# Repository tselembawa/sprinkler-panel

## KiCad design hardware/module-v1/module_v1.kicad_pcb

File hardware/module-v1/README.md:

# Module 4/4, PCB v1 (όλα THT, 100 × 100 mm)

Πλακέτα-βάση για το NUCLEO-G031K8: τροφοδοσία 24 V, RS485 (MAX3485), 4 είσοδοι EOL, 4 ρελέ
changeover, DIP διεύθυνσης με LED. Σχέδιο και αποφάσεις: [docs/module-pcb-v1.md](../../docs/module-pcb-v1.md).

| Αρχείο | Τι είναι |
| --- | --- |
| `module_v1.kicad_pro` | το project: αυτό ανοίγεις στο KiCad |
| `module_v1.kicad_sch` | σχηματικό (οι συνδέσεις γίνονται με ετικέτες ίδιου ονόματος) |
| `module_v1.kicad_pcb` | πλακέτα με τα εξαρτήματα **τοποθετημένα**, χωρίς διαδρόμους ακόμα |
| `bom.csv` | λίστα υλικών |
| `placement.png` | πώς είναι τοποθετημένα (προεπισκόπηση) |
| `parts.py`, `gen.py` | από εδώ βγαίνουν τα παραπάνω (`python gen.py <kicad-footprints>`) |

## Βήματα στο KiCad (8 ή 9)

1. Άνοιξε το `module_v1.kicad_pro`. Αν πει ότι η πλακέτα είναι σε παλιά μορφή και θα μετατραπεί: **OK**.
2. **Σχηματικό**: Inspect → **Electrical Rules Checker** → Run. Στείλε μου ό,τι βγάλει.
3. **PCB Editor**: Tools → **Update PCB from Schematic** (F8). Αν θέλει να **προσθέσει** εξαρτήματα
   (αντί να βρει τα υπάρχοντα), τσέκαρε το **«Re-link footprints to schematic symbols based on their
   reference designators»** και μετά Update. Δεν πρέπει να αλλάξει σχεδόν τίποτα· αν βγάλει λάθη,
   στείλε μου screenshot.
4. **Δρομολόγηση με Freerouting**: Plugin and Content Manager → «Freerouting» → Install.
   Μετά στο PCB: Tools → External Plugins → Freerouting → Start. Περιμένει μερικά λεπτά.
5. Πάτα **B** (γεμίζει η γείωση στην κάτω πλευρά).
6. Inspect → **Design Rules Checker** → Run DRC. Στείλε μου screenshot με τα σφάλματα.
7. Μόνο όταν είναι καθαρό: File → Fabrication Outputs → Gerbers + Drill → zip → JLCPCB.

Οι διάδρομοι για 24 V, GND, 5 V και τις επαφές των ρελέ είναι 1 mm (net class «Power»), το 24 V
του bus από X1 σε X2 2 mm (net class «Bus»), τα σήματα 0,3 mm.

## Πριν την παραγγελία: έλεγχοι με το Nucleo στο χέρι

1. ~~Ποια πλευρά είναι το CN3~~: επιβεβαιωμένο. Με το USB **προς τα πάνω**: CN3 (D1, D0, RST, GND, D2…)
   **αριστερά**, CN4 (VIN, GND, RST, +5V, A7…) **δεξιά**, **pin 1 πάνω** δίπλα στο USB.
2. **Το jumper D2–GND** του Nucleo (CN3 pin 4–5) βγαίνει.
3. **Ρελέ SRD**: το KiCad λέει pin 3 = NO, pin 4 = NC. Με το πρώτο ρελέ στο χέρι, με πολύμετρο:
   ανάμεσα στο COM και στο NC πρέπει να **χτυπάει** (κλειστή) χωρίς τάση στο πηνίο.
4. **Πόσο προεξέχει το Nucleo**: μέτρησε από το κέντρο του pin 1 (D1) μέχρι την άκρη της πλακέτας
   του Nucleo προς το USB, και από το pin 15 (D12) μέχρι την άλλη άκρη. Στο PCB υπάρχουν 12 mm προς
   το USB και 9 mm προς την άλλη πλευρά (μετά είναι η βάση του ULN2003).
5. **A4 και A5 στο breadboard** (δεν έχουν δοκιμαστεί ακόμα): DIP8 μόνο του ON + restart → διεύθυνση 128·
   και το `MOD_DE_PIN` με RS485 module που έχει DE/RE, αν υπάρχει.

## Τι αγοράζεις επιπλέον (δεν είναι στο bom.csv)

- 2 × θηλυκή κεφαλή 1×15, 2,54 mm (για το Nucleo)
- βάση DIP-8 και βάση DIP-16 (για MAX3485 και ULN2003A)
- 1 jumper 2,54 mm (τερματισμός 120 Ω)
- 4 × βίδα M3 + αποστάτες

## Firmware

Στο `firmware/module/mod_app.c`: `#define MOD_BOARD_PCB_V1 1` (DE στο A5, μέτρηση 24 V στο A6).
Στο breadboard μένει `0`.

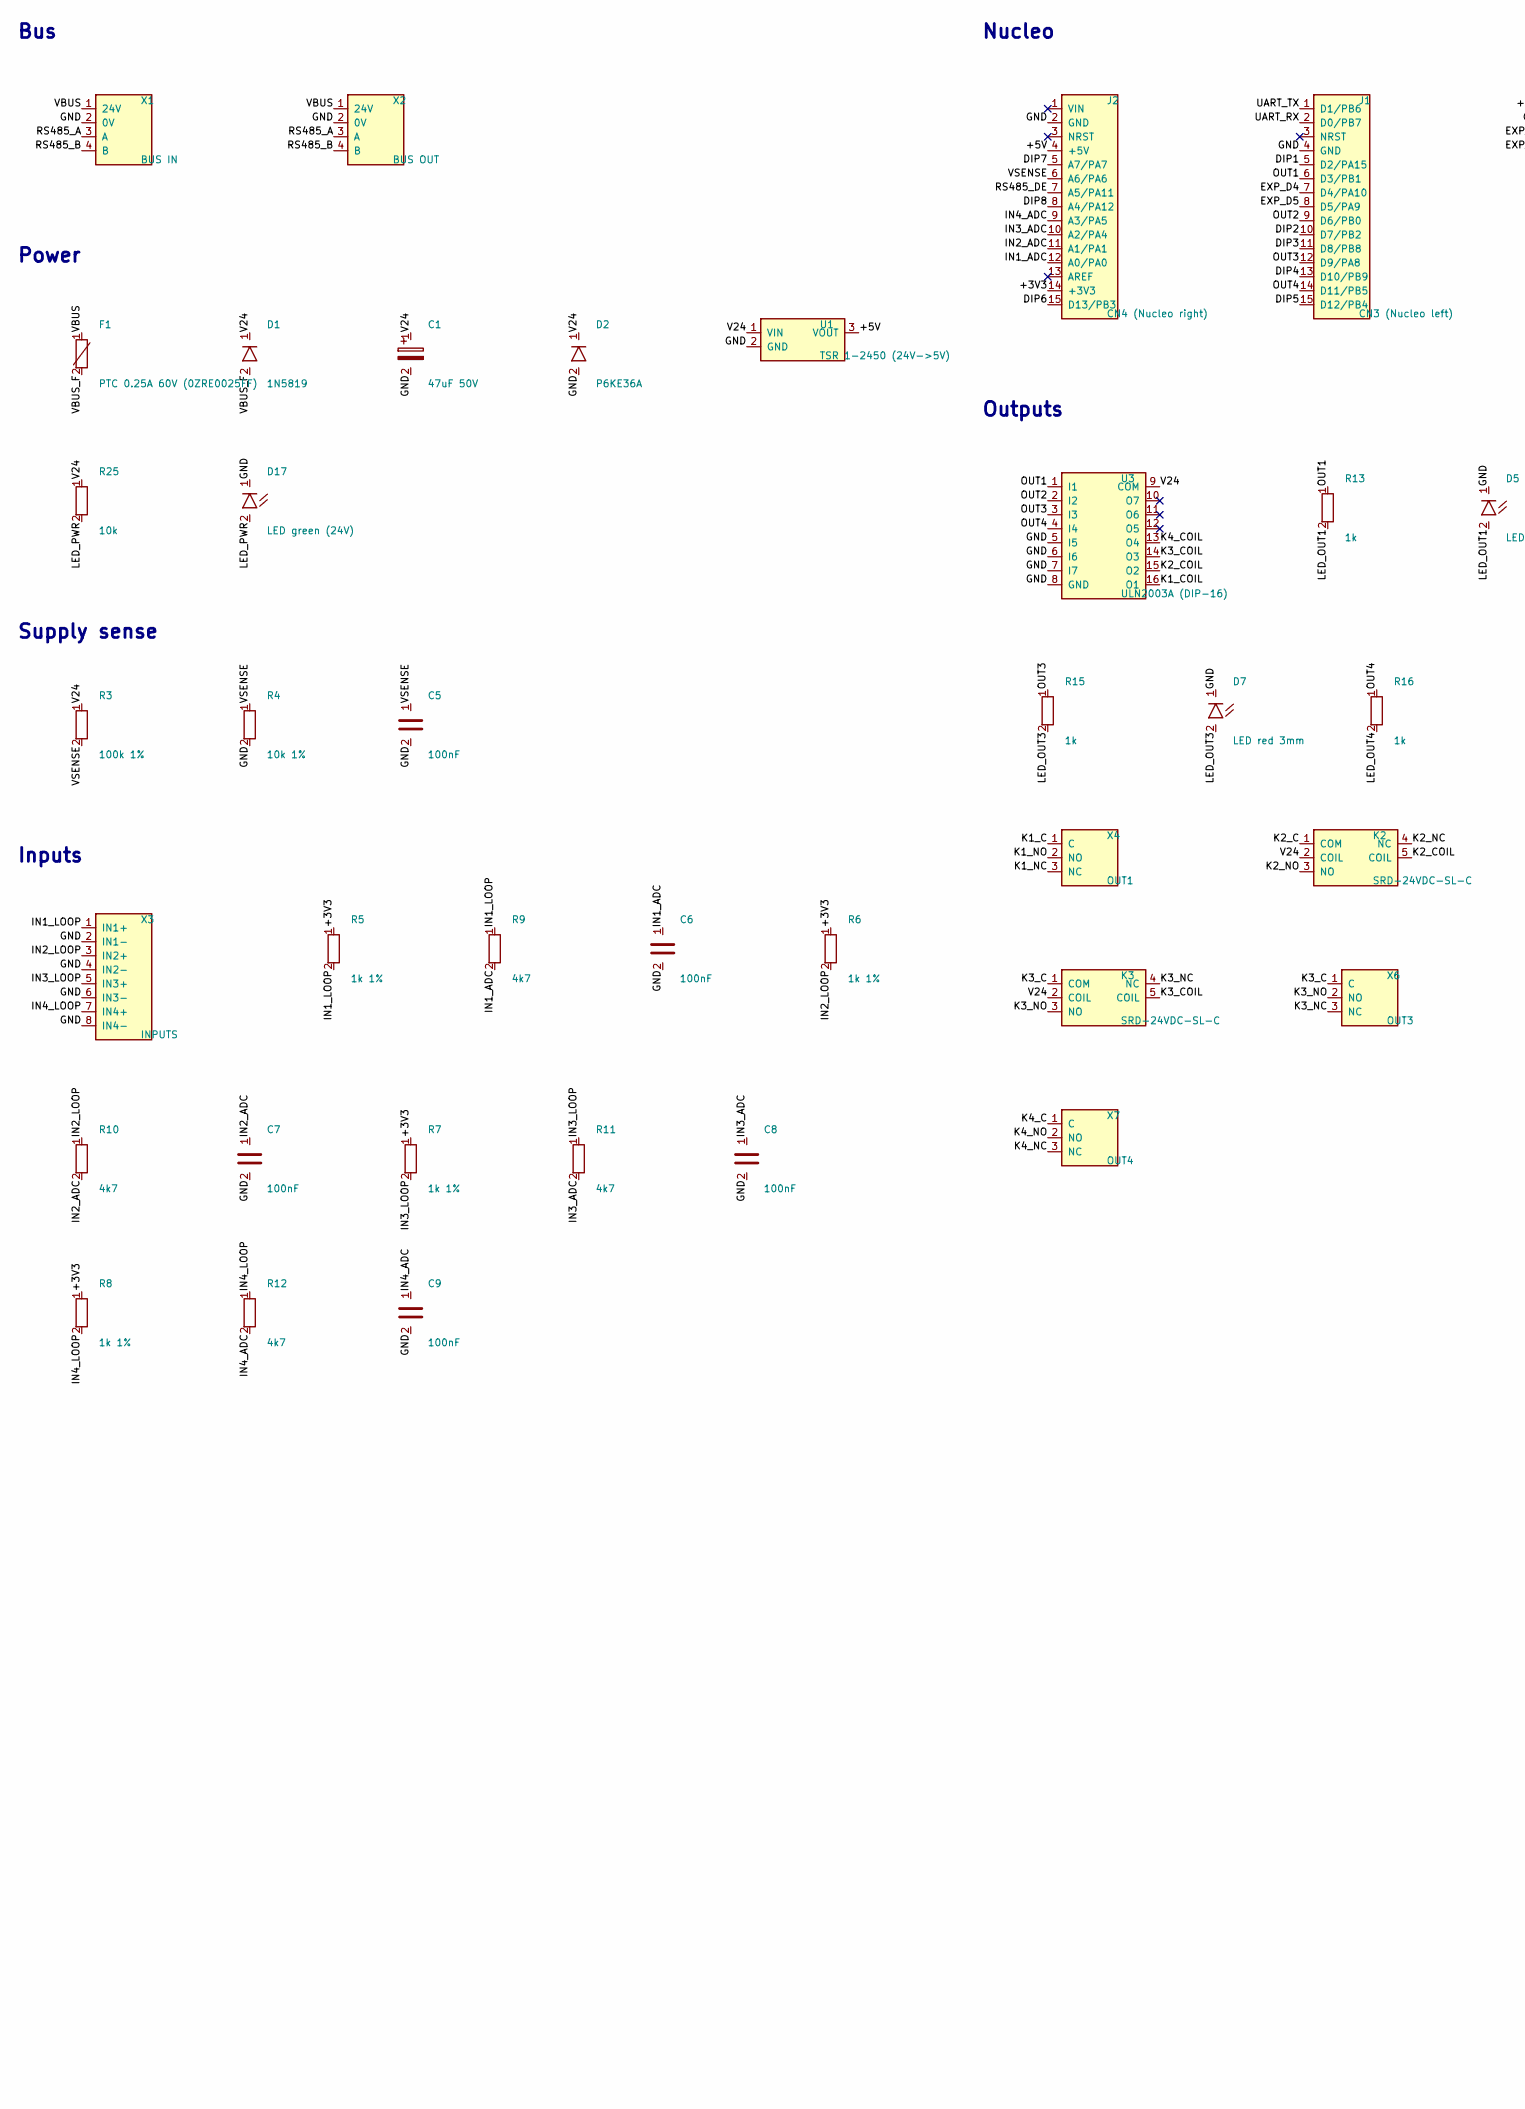
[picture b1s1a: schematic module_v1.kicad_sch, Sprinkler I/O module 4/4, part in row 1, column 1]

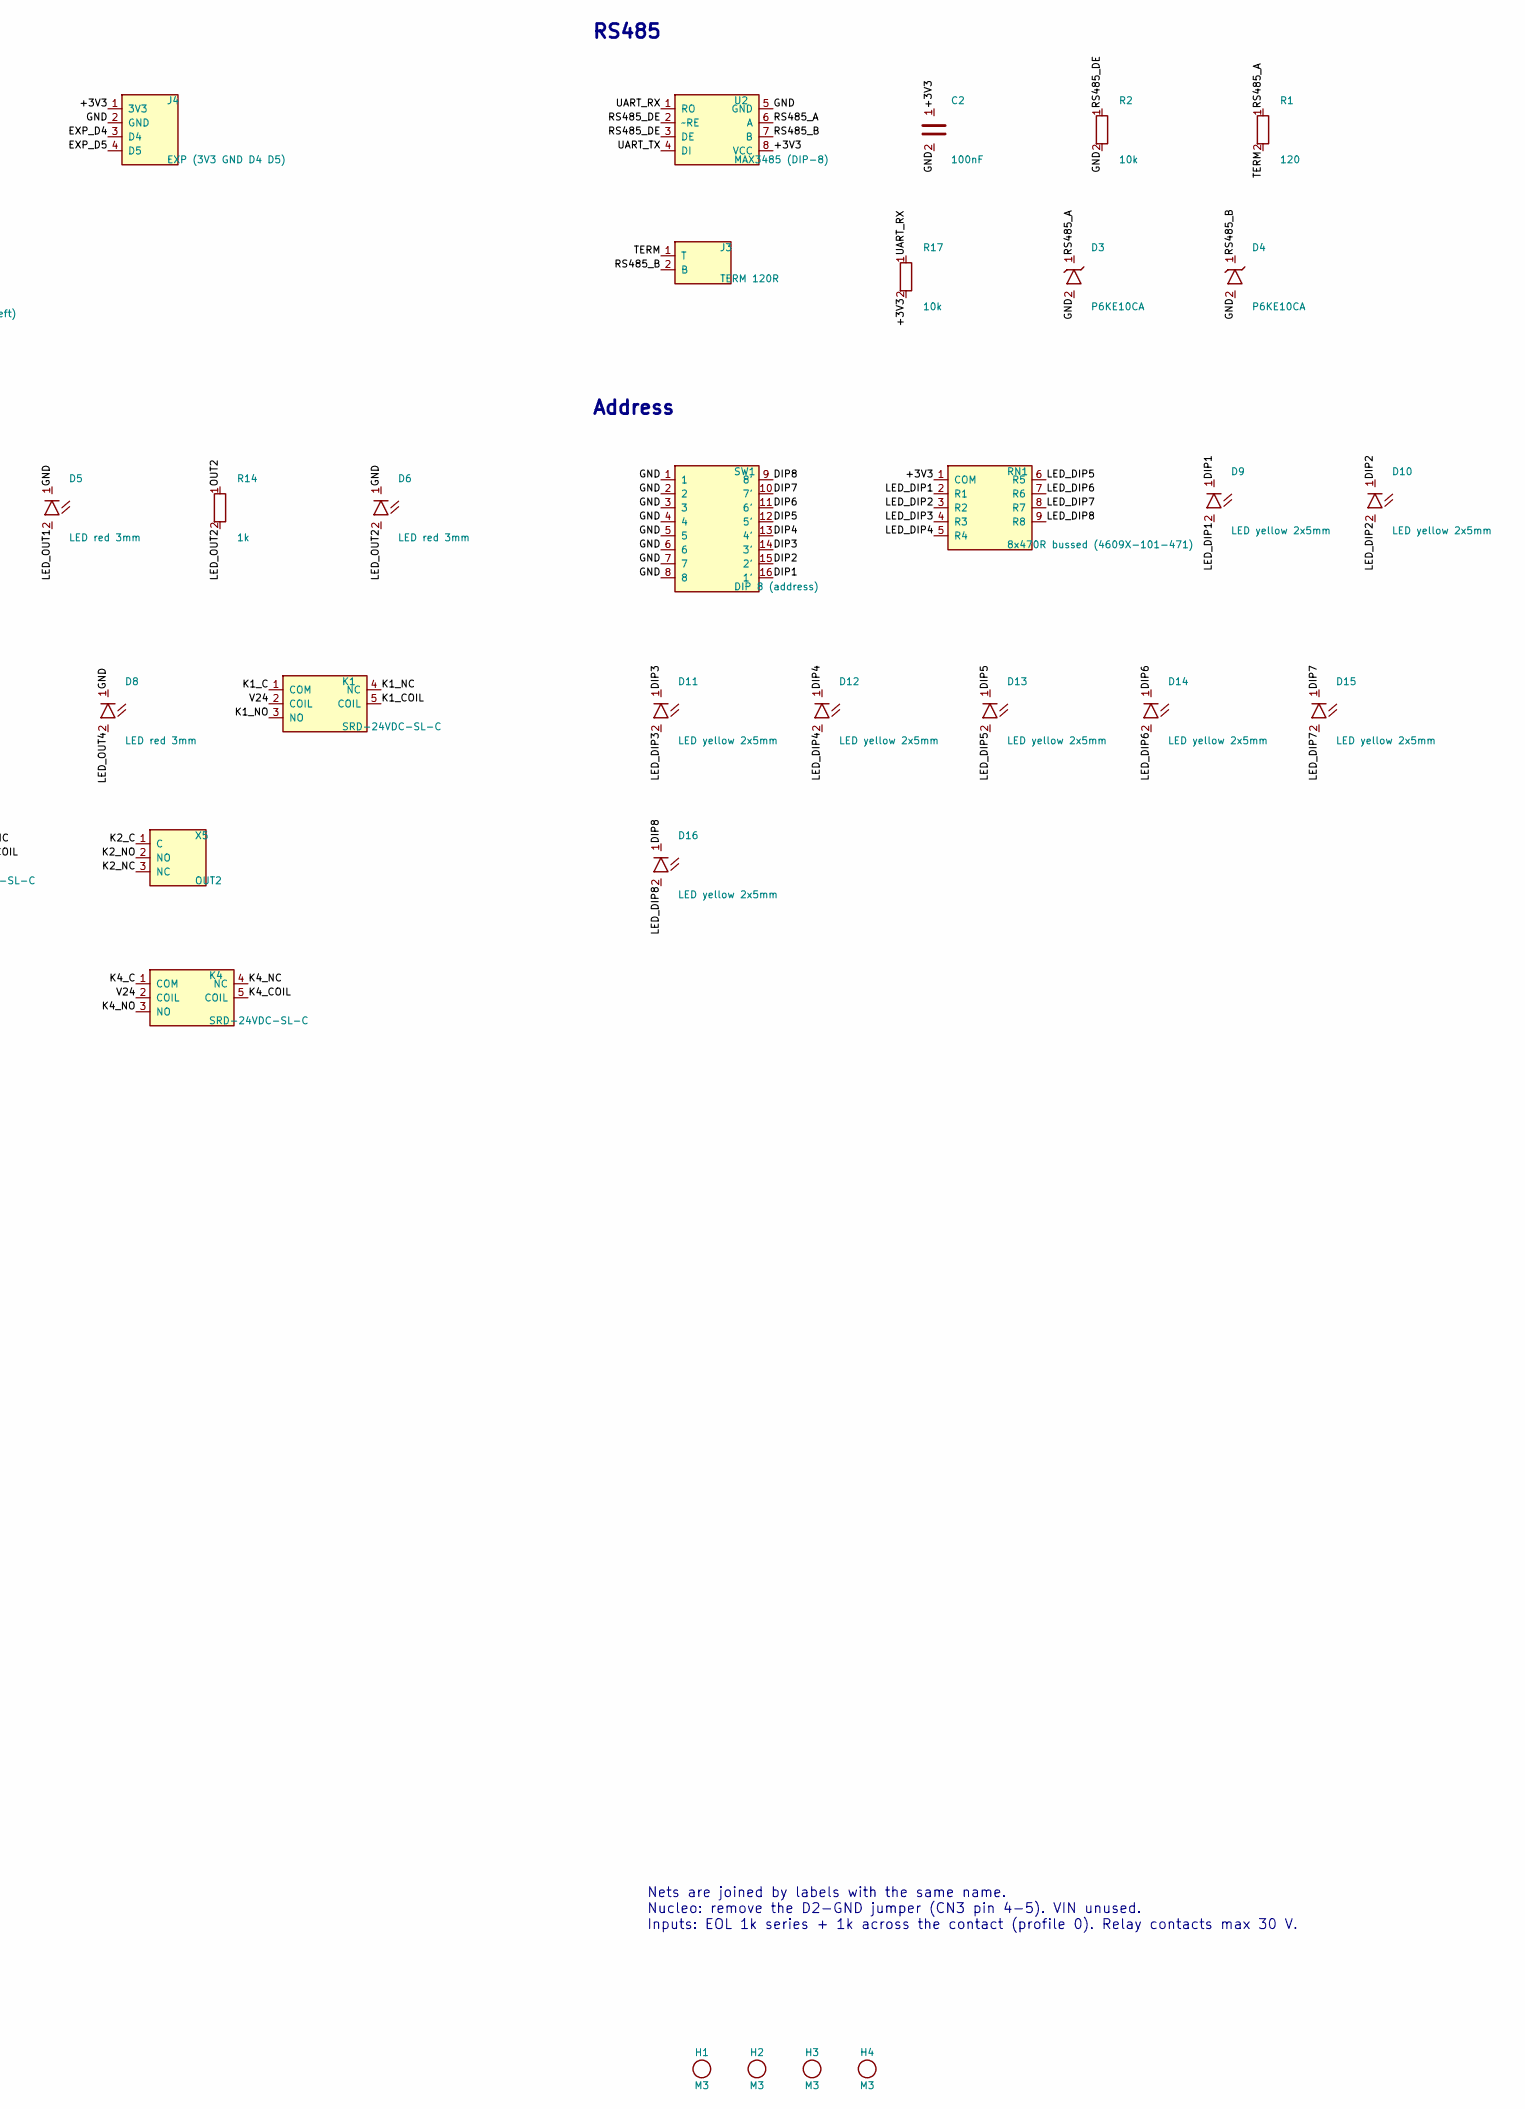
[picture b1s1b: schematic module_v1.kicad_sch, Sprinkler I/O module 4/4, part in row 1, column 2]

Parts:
C1: 47uF 50V; CP_Radial_D8.0mm_P3.50mm
C2, C5, C6, C7, C8, C9: 100nF; C_Disc_D5.0mm_W2.5mm_P5.00mm
D1: 1N5819; D_DO-41_SOD81_P10.16mm_Horizontal
D2: P6KE36A; D_DO-15_P12.70mm_Horizontal
D3, D4: P6KE10CA; D_DO-15_P5.08mm_Vertical_CathodeUp
D5, D6, D7, D8: LED red 3mm; LED_D3.0mm
D9, D10, D11, D12, D13, D14, D15, D16: LED yellow 2x5mm; LED_Rectangular_W5.0mm_H2.0mm
D17: LED green (24V); LED_D3.0mm
F1: PTC 0.25A 60V (0ZRE0025FF); Fuse_BelFuse_0ZRE0025FF_L9.6mm_W3.8mm
H1, H2, H3, H4: M3; MountingHole_3.2mm_M3
J1: CN3 (Nucleo left); PinSocket_1x15_P2.54mm_Vertical
J2: CN4 (Nucleo right); PinSocket_1x15_P2.54mm_Vertical
J3: TERM 120R; PinHeader_1x02_P2.54mm_Vertical
J4: EXP (3V3 GND D4 D5); PinHeader_1x04_P2.54mm_Vertical
K1, K2, K3, K4: SRD-24VDC-SL-C; Relay_SPDT_SANYOU_SRD_Series_Form_C
R1: 120; R_Axial_DIN0207_L6.3mm_D2.5mm_P7.62mm_Horizontal
R2: 10k; R_Axial_DIN0207_L6.3mm_D2.5mm_P7.62mm_Horizontal
R3: 100k 1%; R_Axial_DIN0207_L6.3mm_D2.5mm_P7.62mm_Horizontal
R4: 10k 1%; R_Axial_DIN0207_L6.3mm_D2.5mm_P7.62mm_Horizontal
R5, R6, R7, R8: 1k 1%; R_Axial_DIN0207_L6.3mm_D2.5mm_P7.62mm_Horizontal
R9, R10, R11, R12: 4k7; R_Axial_DIN0207_L6.3mm_D2.5mm_P7.62mm_Horizontal
R13, R14, R15, R16: 1k; R_Axial_DIN0207_L6.3mm_D2.5mm_P2.54mm_Vertical
R17, R25: 10k; R_Axial_DIN0207_L6.3mm_D2.5mm_P2.54mm_Vertical
RN1: 8x470R bussed (4609X-101-471); R_Array_SIP9
SW1: DIP 8 (address); SW_DIP_SPSTx08_Slide_9.78x22.5mm_W7.62mm_P2.54mm
U1: TSR 1-2450 (24V->5V); Converter_DCDC_RECOM_R-78E-0.5_THT
U2: MAX3485 (DIP-8); DIP-8_W7.62mm_Socket
U3: ULN2003A (DIP-16); DIP-16_W7.62mm_Socket
X1: BUS IN; TerminalBlock_Phoenix_MKDS-1,5-4-5.08_1x04_P5.08mm_Horizont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
X2: BUS OUT; TerminalBlock_Phoenix_MKDS-1,5-4-5.08_1x04_P5.08mm_Horizont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
X3: INPUTS; TerminalBlock_Phoenix_MKDS-1,5-8-5.08_1x08_P5.08mm_Horizont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
X4: OUT1; TerminalBlock_Phoenix_MKDS-1,5-3-5.08_1x03_P5.08mm_Horizont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
X5: OUT2; TerminalBlock_Phoenix_MKDS-1,5-3-5.08_1x03_P5.08mm_Horizont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
X6: OUT3; TerminalBlock_Phoenix_MKDS-1,5-3-5.08_1x03_P5.08mm_Horizont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
X7: OUT4; TerminalBlock_Phoenix_MKDS-1,5-3-5.08_1x03_P5.08mm_Horizont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

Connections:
+3V3: C2.1, J2.14 (+3V3), J4.1 (3V3), R5.1, R6.1, R7.1, R8.1, R17.2, RN1.1 (COM), U2.8 (VCC)
+5V: J2.4 (+5V), U1.3 (VOUT)
DIP1: D9.1, J1.5 (D2/PA15), SW1.16 (1')
DIP2: D10.1, J1.10 (D7/PB2), SW1.15 (2')
DIP3: D11.1, J1.11 (D8/PB8), SW1.14 (3')
DIP4: D12.1, J1.13 (D10/PB9), SW1.13 (4')
DIP5: D13.1, J1.15 (D12/PB4), SW1.12 (5')
DIP6: D14.1, J2.15 (D13/PB3), SW1.11 (6')
DIP7: D15.1, J2.5 (A7/PA7), SW1.10 (7')
DIP8: D16.1, J2.8 (A4/PA12), SW1.9 (8')
EXP_D4: J1.7 (D4/PA10), J4.3 (D4)
EXP_D5: J1.8 (D5/PA9), J4.4 (D5)
GND: C1.2, C2.2, C5.2, C6.2, C7.2, C8.2, C9.2, D2.2, D3.2, D4.2, D5.1, D6.1, D7.1, D8.1, D17.1, J1.4 (GND), J2.2 (GND), J4.2 (GND), R2.2, R4.2, SW1.1, SW1.2, SW1.3, SW1.4, SW1.5, SW1.6, SW1.7, SW1.8, U1.2 (GND), U2.5 (GND), U3.5 (I5), U3.6 (I6), U3.7 (I7), U3.8 (GND), X1.2 (0V), X2.2 (0V), X3.2 (IN1-), X3.4 (IN2-), X3.6 (IN3-), X3.8 (IN4-)
IN1_ADC: C6.1, J2.12 (A0/PA0), R9.2
IN1_LOOP: R5.2, R9.1, X3.1 (IN1+)
IN2_ADC: C7.1, J2.11 (A1/PA1), R10.2
IN2_LOOP: R6.2, R10.1, X3.3 (IN2+)
IN3_ADC: C8.1, J2.10 (A2/PA4), R11.2
IN3_LOOP: R7.2, R11.1, X3.5 (IN3+)
IN4_ADC: C9.1, J2.9 (A3/PA5), R12.2
IN4_LOOP: R8.2, R12.1, X3.7 (IN4+)
K1_C: K1.1 (COM), X4.1 (C)
K1_COIL: K1.5 (COIL), U3.16 (O1)
K1_NC: K1.4 (NC), X4.3 (NC)
K1_NO: K1.3 (NO), X4.2 (NO)
K2_C: K2.1 (COM), X5.1 (C)
K2_COIL: K2.5 (COIL), U3.15 (O2)
K2_NC: K2.4 (NC), X5.3 (NC)
K2_NO: K2.3 (NO), X5.2 (NO)
K3_C: K3.1 (COM), X6.1 (C)
K3_COIL: K3.5 (COIL), U3.14 (O3)
K3_NC: K3.4 (NC), X6.3 (NC)
K3_NO: K3.3 (NO), X6.2 (NO)
K4_C: K4.1 (COM), X7.1 (C)
K4_COIL: K4.5 (COIL), U3.13 (O4)
K4_NC: K4.4 (NC), X7.3 (NC)
K4_NO: K4.3 (NO), X7.2 (NO)
LED_DIP1: D9.2, RN1.2 (R1)
LED_DIP2: D10.2, RN1.3 (R2)
LED_DIP3: D11.2, RN1.4 (R3)
LED_DIP4: D12.2, RN1.5 (R4)
LED_DIP5: D13.2, RN1.6 (R5)
LED_DIP6: D14.2, RN1.7 (R6)
LED_DIP7: D15.2, RN1.8 (R7)
LED_DIP8: D16.2, RN1.9 (R8)
LED_OUT1: D5.2, R13.2
LED_OUT2: D6.2, R14.2
LED_OUT3: D7.2, R15.2
LED_OUT4: D8.2, R16.2
LED_PWR: D17.2, R25.2
OUT1: J1.6 (D3/PB1), R13.1, U3.1 (I1)
OUT2: J1.9 (D6/PB0), R14.1, U3.2 (I2)
OUT3: J1.12 (D9/PA8), R15.1, U3.3 (I3)
OUT4: J1.14 (D11/PB5), R16.1, U3.4 (I4)
RS485_A: D3.1, R1.1, U2.6 (A), X1.3 (A), X2.3 (A)
RS485_B: D4.1, J3.2 (B), U2.7 (B), X1.4 (B), X2.4 (B)
RS485_DE: J2.7 (A5/PA11), R2.1, U2.2 (~RE), U2.3 (DE)
TERM: J3.1 (T), R1.2
UART_RX: J1.2 (D0/PB7), R17.1, U2.1 (RO)
UART_TX: J1.1 (D1/PB6), U2.4 (DI)
V24: C1.1, D1.1, D2.1, K1.2 (COIL), K2.2 (COIL), K3.2 (COIL), K4.2 (COIL), R3.1, R25.1, U1.1 (VIN), U3.9 (COM)
VBUS: F1.1, X1.1 (24V), X2.1 (24V)
VBUS_F: D1.2, F1.2
VSENSE: C5.1, J2.6 (A6/PA6), R3.2, R4.1

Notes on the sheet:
Bus
Power
Supply sense
Inputs
Nucleo
Outputs
RS485
Address
Nets are joined by labels with the same name. Nucleo: remove the D2-GND jumper (CN3 pin 4-5). VIN unused. Inputs: EOL 1k series + 1k across the contact (profile 0). Relay contacts max 30 V.

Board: 2 copper layers, 67 parts (0 on the bottom side), 64 nets, no tracks yet.

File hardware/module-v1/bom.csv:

qty;value;refs;footprint
1;47uF 50V;C1;CP_Radial_D8.0mm_P3.50mm
6;100nF;C2 C5 C6 C7 C8 C9;C_Disc_D5.0mm_W2.5mm_P5.00mm
1;1N5819;D1;D_DO-41_SOD81_P10.16mm_Horizontal
1;P6KE36A;D2;D_DO-15_P12.70mm_Horizontal
2;P6KE10CA;D3 D4;D_DO-15_P5.08mm_Vertical_CathodeUp
4;LED red 3mm;D5 D6 D7 D8;LED_D3.0mm
8;LED yellow 2x5mm;D9 D10 D11 D12 D13 D14 D15 D16;LED_Rectangular_W5.0mm_H2.0mm
1;LED green (24V);D17;LED_D3.0mm
1;PTC 0.25A 60V (0ZRE0025FF);F1;Fuse_BelFuse_0ZRE0025FF_L9.6mm_W3.8mm
1;CN3 (Nucleo left);J1;PinSocket_1x15_P2.54mm_Vertical
1;CN4 (Nucleo right);J2;PinSocket_1x15_P2.54mm_Vertical
1;TERM 120R;J3;PinHeader_1x02_P2.54mm_Vertical
1;EXP (3V3 GND D4 D5);J4;PinHeader_1x04_P2.54mm_Vertical
4;SRD-24VDC-SL-C;K1 K2 K3 K4;Relay_SPDT_SANYOU_SRD_Series_Form_C
1;120;R1;R_Axial_DIN0207_L6.3mm_D2.5mm_P7.62mm_Horizontal
1;10k;R2;R_Axial_DIN0207_L6.3mm_D2.5mm_P7.62mm_Horizontal
1;100k 1%;R3;R_Axial_DIN0207_L6.3mm_D2.5mm_P7.62mm_Horizontal
1;10k 1%;R4;R_Axial_DIN0207_L6.3mm_D2.5mm_P7.62mm_Horizontal
4;1k 1%;R5 R6 R7 R8;R_Axial_DIN0207_L6.3mm_D2.5mm_P7.62mm_Horizontal
4;4k7;R9 R10 R11 R12;R_Axial_DIN0207_L6.3mm_D2.5mm_P7.62mm_Horizontal
4;1k;R13 R14 R15 R16;R_Axial_DIN0207_L6.3mm_D2.5mm_P2.54mm_Vertical
2;10k;R17 R25;R_Axial_DIN0207_L6.3mm_D2.5mm_P2.54mm_Vertical
1;8x470R bussed (4609X-101-471);RN1;R_Array_SIP9
1;DIP 8 (address);SW1;SW_DIP_SPSTx08_Slide_9.78x22.5mm_W7.62mm_P2.54mm
1;TSR 1-2450 (24V->5V);U1;Converter_DCDC_RECOM_R-78E-0.5_THT
1;MAX3485 (DIP-8);U2;DIP-8_W7.62mm_Socket
1;ULN2003A (DIP-16);U3;DIP-16_W7.62mm_Socket
1;BUS IN;X1;TerminalBlock_Phoenix_MKDS-1,5-4-5.08_1x04_P5.08mm_Horizontal
1;BUS OUT;X2;TerminalBlock_Phoenix_MKDS-1,5-4-5.08_1x04_P5.08mm_Horizontal
1;INPUTS;X3;TerminalBlock_Phoenix_MKDS-1,5-8-5.08_1x08_P5.08mm_Horizontal
1;OUT1;X4;TerminalBlock_Phoenix_MKDS-1,5-3-5.08_1x03_P5.08mm_Horizontal
1;OUT2;X5;TerminalBlock_Phoenix_MKDS-1,5-3-5.08_1x03_P5.08mm_Horizontal
1;OUT3;X6;TerminalBlock_Phoenix_MKDS-1,5-3-5.08_1x03_P5.08mm_Horizontal
1;OUT4;X7;TerminalBlock_Phoenix_MKDS-1,5-3-5.08_1x03_P5.08mm_Horizontal

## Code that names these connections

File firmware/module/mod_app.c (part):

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 * I/O module on the NUCLEO-G031K8 (breadboard, or the PCB v1 with MOD_BOARD_PCB_V1): the STM32 side.
 * Measures, switches pins, moves bytes. Everything the module decides is in mod_core.c.
 *
 * CubeMX (project "Module"): USART1 on PB6/PB7, Asynchronous, 38400 8N1, NVIC "USART1 global
 * interrupt" on. USART2 (ST-LINK, 115200) as the board gives it. Nothing else: GPIO, ADC and
 * watchdog are set up here (the ADC with registers, so no ADC driver is needed in CubeMX).
 *
 *   RS485 module   RO -> D0 (PB7, USART1_RX)   DI <- D1 (PB6, USART1_TX)   (DE/RE: see MOD_DE_PIN)
 *   Inputs  IN1 A0 (PA0)  IN2 A1 (PA1)  IN3 A2 (PA4)  IN4 A3 (PA5):
 *           3V3 - 1 kOhm - pin - loop (1 kOhm in series, contact with 1 kOhm across) - GND
 *   Outputs OUT1 D3 (PB1)  OUT2 D6 (PB0)  OUT3 D9 (PA8)  OUT4 D11 (PB5): LED + 330 Ohm to GND
 *   DIP     1 D2 (PA15)  2 D7 (PB2)  3 D8 (PB8)  4 D10 (PB9)  5 D12 (PB4)  6 D13 (PB3)
 *           7 A7 (PA7)  8 A4 (PA12): ON = to GND, address = sum (1, 2, 4, ... 128)
 *   LED     LD3 on the board (PC6): short blink = fine, slow = no controller, fast = IDENTIFY
 *   Supply  A6 (PA6): 24 V through 100 kOhm / 10 kOhm (MOD_SUPPLY_RTOP/RBOT; 0 = not fitted)
 */
#include "mod_app.h"

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#if MOD_BOARD_PCB_V1
#define MOD_SUPPLY_RTOP    100000u
#define MOD_SUPPLY_DIODE_MV 350u       /* 1N5819 in front of the divider */
#define MOD_DE_PIN         GPIO_PIN_11 /* A5 (PA11) to DE and /RE */
#else
#define MOD_SUPPLY_RTOP    0u          /* 0 = not fitted: the module reports 24.0 V */
#define MOD_SUPPLY_DIODE_MV 0u
/* #define MOD_DE_PIN  GPIO_PIN_11       RS485 module with DE/RE (MAX485): A5 (PA11). The
                                         modules with automatic direction need nothing. */
#endif
#define WATCHDOG_MS        1000u
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
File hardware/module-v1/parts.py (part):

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}

# Nucleo-32 headers (UM2591 table 9, MB1455 schematic)
CN3 = {1: "D1/PB6", 2: "D0/PB7", 3: "NRST", 4: "GND", 5: "D2/PA15", 6: "D3/PB1", 7: "D4/PA10",
       8: "D5/PA9", 9: "D6/PB0", 10: "D7/PB2", 11: "D8/PB8", 12: "D9/PA8", 13: "D10/PB9",
       14: "D11/PB5", 15: "D12/PB4"}
CN4 = {1: "VIN", 2: "GND", 3: "NRST", 4: "+5V", 5: "A7/PA7", 6: "A6/PA6", 7: "A5/PA11",
       8: "A4/PA12", 9: "A3/PA5", 10: "A2/PA4", 11: "A1/PA1", 12: "A0/PA0", 13: "AREF",
       14: "+3V3", 15: "D13/PB3"}

NC = None   # pin left unconnected

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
